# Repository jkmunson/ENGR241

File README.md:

# ENGR241
This was an old repository used to collaborate on group projects in ENGR241, Circuits II

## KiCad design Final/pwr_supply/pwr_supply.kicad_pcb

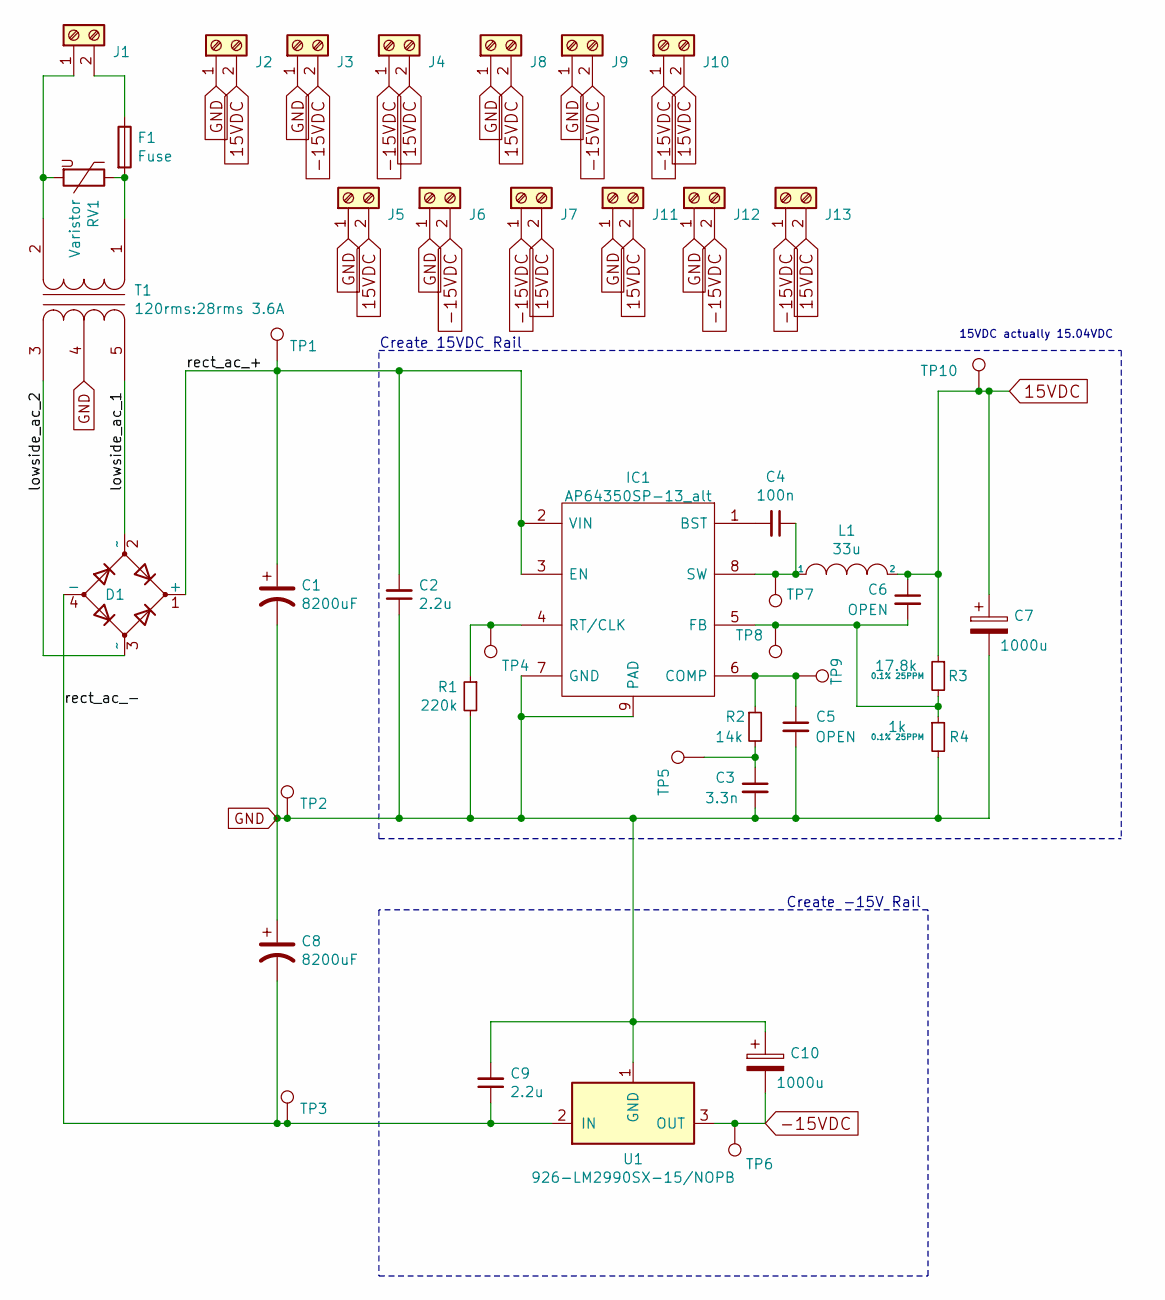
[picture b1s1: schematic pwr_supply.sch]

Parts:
C1, C8: 8200uF; CP_Radial_D30.0mm_P10.00mm_SnapIn
C2, C9: 2.2u; C_1210_3225Metric_Pad1.42x2.65mm_HandSolder
C3: 3.3n; C_1210_3225Metric_Pad1.42x2.65mm_HandSolder
C4: 100n; C_1210_3225Metric_Pad1.42x2.65mm_HandSolder
C5, C6: OPEN; C_1210_3225Metric_Pad1.42x2.65mm_HandSolder
C7, C10: 1000u; CP_Radial_D16.0mm_P7.50mm
D1: D_Bridge_+AA-; Diode_Bridge_19.0x3.5x10.0mm_P5.0mm
F1: Fuse; 00318370
IC1: AP64350SP-13_alt; SOIC127P600X163-9N; Mouser Part Number 621-AP64350SP-13
J1, J2, J3, J4, J5, J6, J7, J8, J9, J10, J11, J12, J13: Screw_Terminal_01x02; TerminalBlock_bornier-2_P5.08mm
L1: 33u; 12RS333C
R1: 220k; C_1210_3225Metric_Pad1.42x2.65mm_HandSolder
R2: 14k; C_1210_3225Metric_Pad1.42x2.65mm_HandSolder
R3: 17.8k; C_1210_3225Metric_Pad1.42x2.65mm_HandSolder; Tolerance 0.1% 25PPM
R4: 1k; C_1210_3225Metric_Pad1.42x2.65mm_HandSolder; Tolerance 0.1% 25PPM
RV1: Varistor; RV_Disc_D16.5mm_W6.7mm_P7.5mm
T1: 120rms:28rms 3.6A; Transformer_Entry
TP1, TP2, TP3, TP4, TP5, TP6, TP7, TP8, TP9, TP10: TestPoint; PinHeader_1x01_P2.54mm_Vertical
U1: 926-LM2990SX-15/NOPB; TO-263-3_TabPin2

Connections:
15VDC: C6.1, C7.1, J2.2, J4.2, J5.2, J7.2, J8.2, J10.2, J11.2, J13.2, L1.2, L1.4, R3.1, TP10.1
-15VDC: C10.2, J3.2, J4.1, J6.2, J7.1, J9.2, J10.1, J12.2, J13.1, TP6.1, U1.3 (OUT)
/lowside_ac_1: D1.2 (~~), T1.5 (SB)
/lowside_ac_2: D1.3 (~~), T1.3 (SA)
/rect_ac_+: C1.1, C2.2, D1.1 (+), IC1.2 (VIN), IC1.3 (EN), TP1.1
/rect_ac_-: C8.2, C9.1, D1.4 (-), TP3.1, U1.2 (IN)
GND: C1.2, C2.1, C3.2, C5.2, C7.2, C8.1, C9.2, C10.1, IC1.7 (GND), IC1.9 (PAD), J2.1, J3.1, J5.1, J6.1, J8.1, J9.1, J11.1, J12.1, R1.2, R4.2, T1.4 (SC), TP2.1, U1.1 (GND)
unnamed: C3.1, R2.2, TP5.1
unnamed: C4.1, IC1.8 (SW), L1.1, L1.3, TP7.1
unnamed: C4.2, IC1.1 (BST)
unnamed: C5.1, IC1.6 (COMP), R2.1, TP9.1
unnamed: C6.2, IC1.5 (FB), R3.2, R4.1, TP8.1
unnamed: F1.1, J1.2
unnamed: F1.2, RV1.1, T1.1 (AA)
unnamed: IC1.4 (RT/CLK), R1.1, TP4.1
unnamed: J1.1, RV1.2, T1.2 (AB)

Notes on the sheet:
Create 15VDC Rail
15VDC actually 15.04VDC
Create -15V Rail

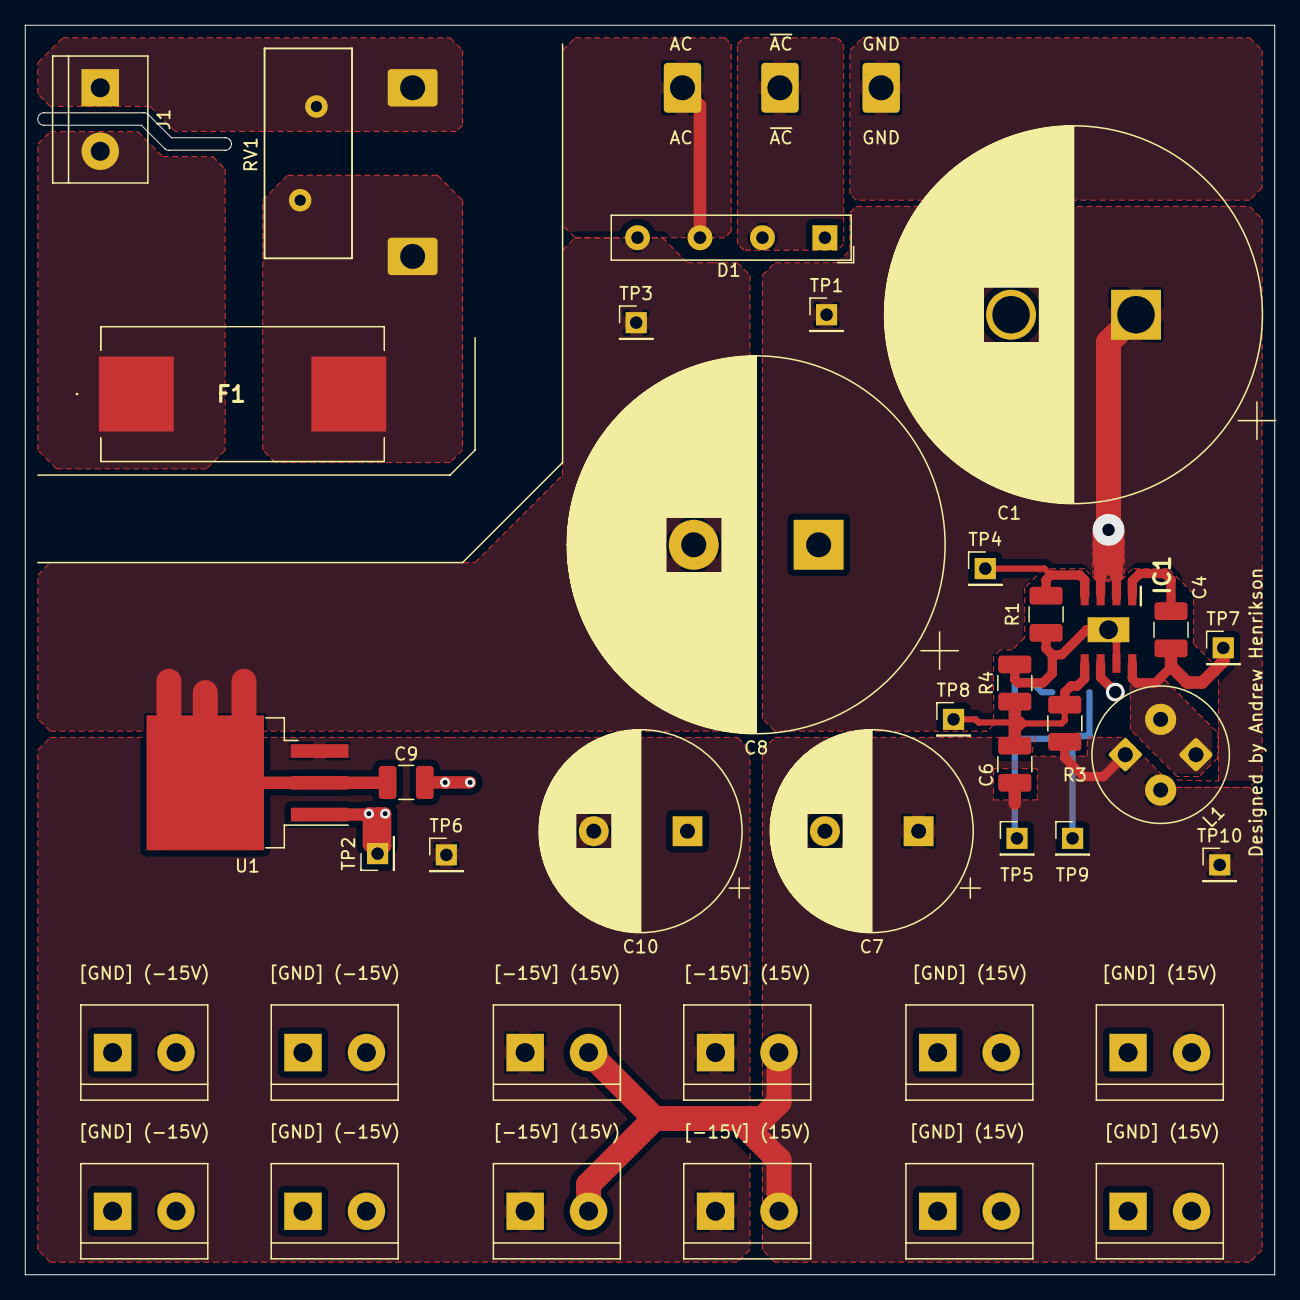
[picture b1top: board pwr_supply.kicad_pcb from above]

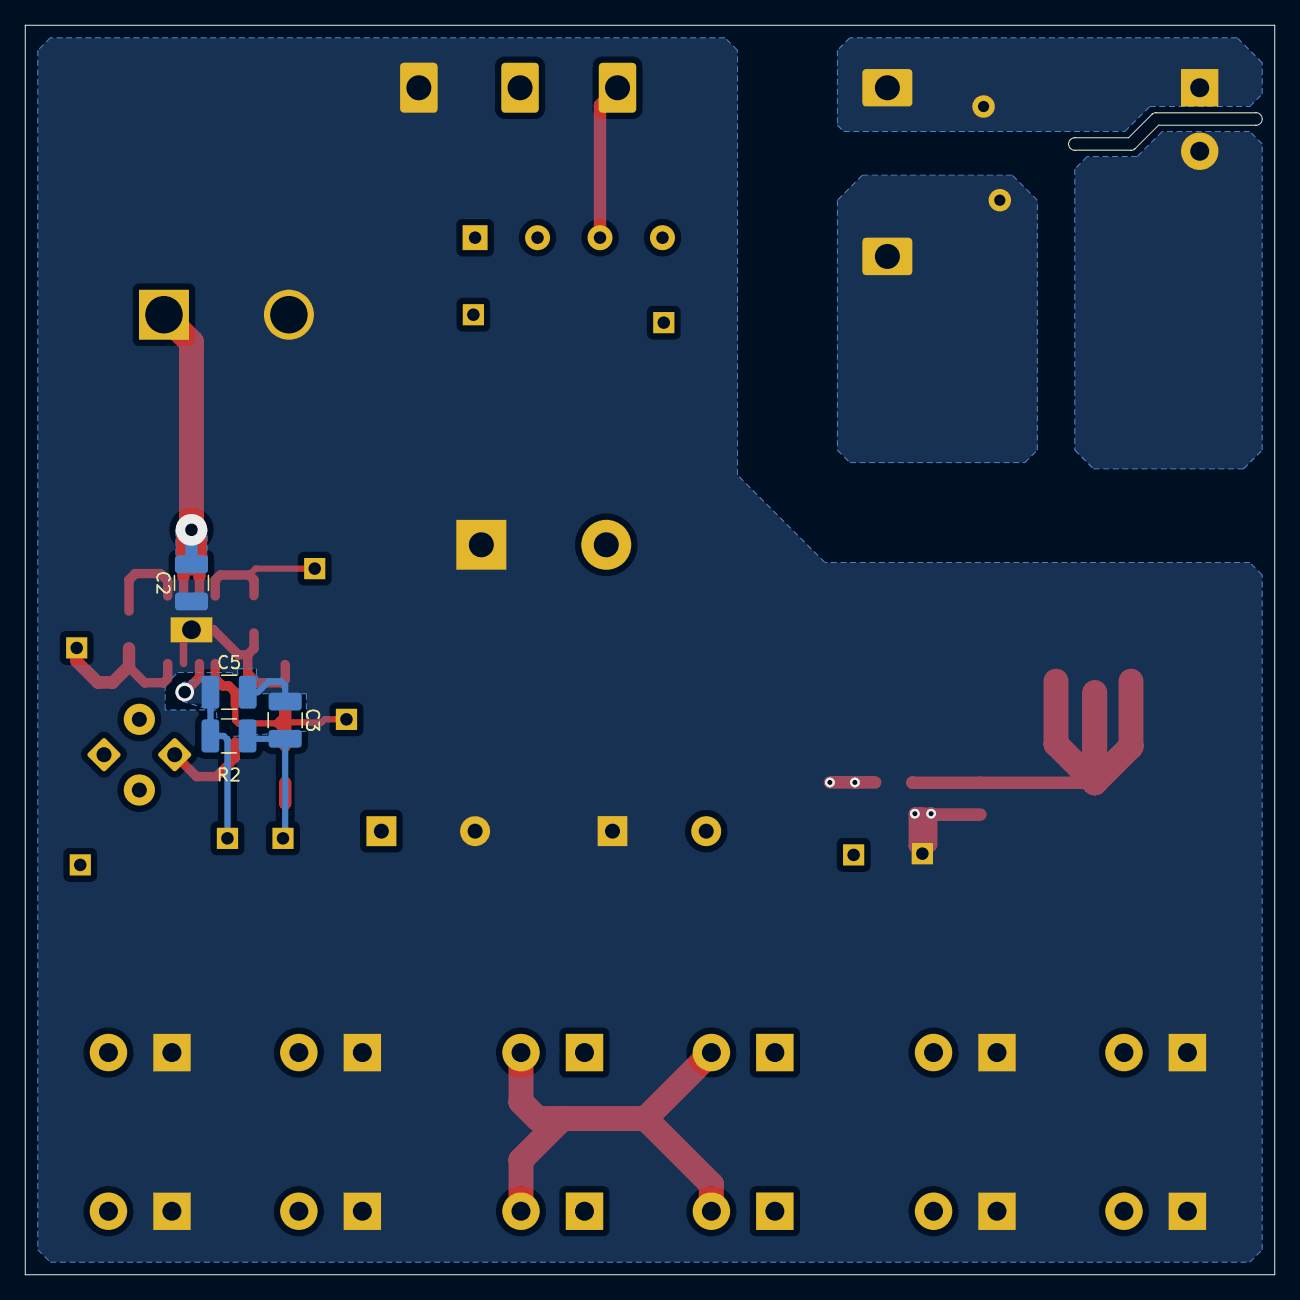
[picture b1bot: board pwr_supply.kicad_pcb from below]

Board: 2 copper layers, 100.0 x 100.0 mm, 44 parts (4 on the bottom side), 16 nets.

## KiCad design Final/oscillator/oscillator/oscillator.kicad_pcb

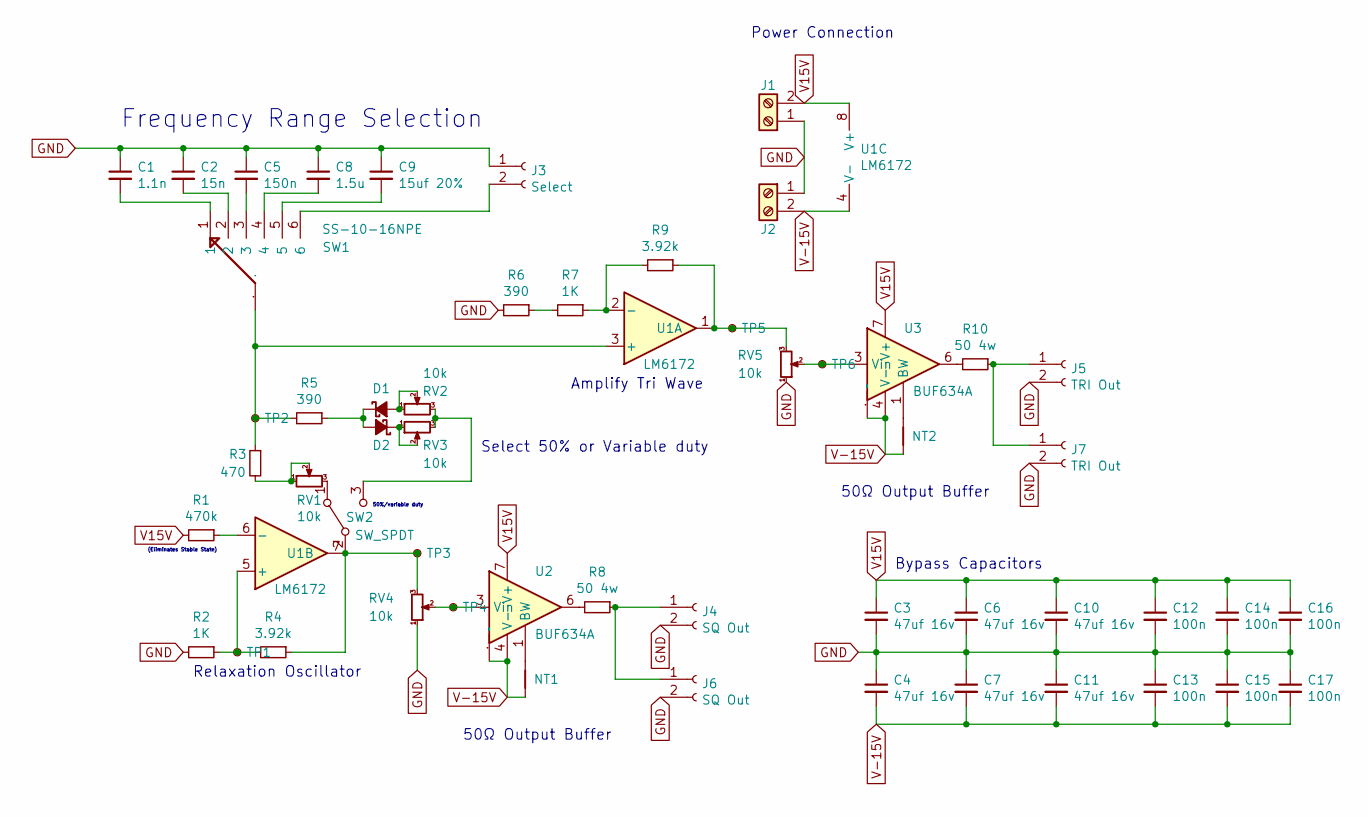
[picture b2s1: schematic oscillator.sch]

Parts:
C1: 1.1n; C_1210_3225Metric_Pad1.42x2.65mm_HandSolder
C2: 15n; C_1210_3225Metric_Pad1.42x2.65mm_HandSolder
C3, C4, C6, C7, C10, C11: 47uf 16v; C_1210_3225Metric_Pad1.42x2.65mm_HandSolder
C5: 150n; C_1210_3225Metric_Pad1.42x2.65mm_HandSolder
C8: 1.5u; C_1210_3225Metric_Pad1.42x2.65mm_HandSolder
C9: 15uf 20%; C_1210_3225Metric_Pad1.42x2.65mm_HandSolder
C12, C13, C14, C15, C16, C17: 100n; C_1210_3225Metric_Pad1.42x2.65mm_HandSolder
D1, D2: sch; D_SOD-123F
J1, J2: V15V_IN; TerminalBlock_bornier-2_P5.08mm
J3: Select; PinHeader_1x02_P2.54mm_Vertical
J4, J6: SQ Out; PinHeader_1x02_P2.54mm_Vertical
J5, J7: TRI Out; PinHeader_1x02_P2.54mm_Vertical
NT1, NT2: Net-Tie_2; SolderJumper-2_P1.3mm_Open_TrianglePad1.0x1.5mm
R1: 470k; C_1210_3225Metric_Pad1.42x2.65mm_HandSolder
R2, R7: 1K; R_1210_3225Metric_Pad1.42x2.65mm_HandSolder
R3: 470; R_1210_3225Metric_Pad1.42x2.65mm_HandSolder
R4, R9: 3.92k; R_1210_3225Metric_Pad1.42x2.65mm_HandSolder
R5, R6: 390; R_1210_3225Metric_Pad1.42x2.65mm_HandSolder
R8, R10: 50 4w; R_2816_7142Metric_Pad3.20x4.45mm_HandSolder
RV1, RV2, RV3, RV4, RV5: 10k; RK09K1130A5R
SW1: SS-10-16NPE; SS-10-16NP-E
SW2: SW_SPDT; 100SP1T1B4M2QE
TP1, TP2, TP3, TP4, TP5, TP6: TestPoint_Small; PinHeader_1x01_P1.00mm_Vertical
U1: LM6172; SOIC-8_3.9x4.9mm_P1.27mm
U2, U3: BUF634A; SOIC-8-1EP_3.9x4.9mm_P1.27mm_EP2.514x3.2mm_ThermalVias; Mouser# BUF634AIDR

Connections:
GND: C1.1, C2.1, C3.2, C4.1, C5.1, C6.2, C7.1, C8.1, C9.1, C10.2, C11.1, C12.2, C13.1, C14.2, C15.1, C16.2, C17.1, J1.1, J2.1, J3.1, J4.2, J5.2, J6.2, J7.2, R2.2, R6.2, RV4.1, RV5.1
unnamed: C1.2, SW1.1
unnamed: C2.2, SW1.2
unnamed: C5.2, SW1.3
unnamed: C8.2, SW1.4
unnamed: C9.2, SW1.5
unnamed: D1.1 (K), D2.2 (A), R5.1
unnamed: D1.2 (A), RV2.1, RV2.2
unnamed: D2.1 (K), RV3.1, RV3.2
unnamed: J3.2, SW1.6
unnamed: J4.1, J6.1, R8.1
unnamed: J5.1, J7.1, R10.1
unnamed: NT1.1, U2.1 (BW)
unnamed: NT2.1, U3.1 (BW)
unnamed: R1.1, U1.6 (-)
unnamed: R2.1, R4.2, TP1.1, U1.5 (+)
unnamed: R3.1, R5.2, SW1.C, TP2.1, U1.3 (+)
unnamed: R3.2, RV1.1, RV1.2
unnamed: R4.1, RV4.3, SW2.2 (B), TP3.1, U1.7
unnamed: R6.1, R7.2
unnamed: R7.1, R9.2, U1.2 (-)
unnamed: R8.2, U2.6
unnamed: R9.1, RV5.3, TP5.1, U1.1
unnamed: R10.2, U3.6
unnamed: RV1.3, SW2.1 (A)
unnamed: RV2.3, RV3.3, SW2.3 (C)
unnamed: RV4.2, TP4.1, U2.3 (Vin)
unnamed: RV5.2, TP6.1, U3.3 (Vin)
V15V: C3.1, C6.1, C10.1, C12.1, C14.1, C16.1, J1.2, R1.2, U1.8 (V+), U2.7 (V+), U3.7 (V+)
V-15V: C4.2, C7.2, C11.2, C13.2, C15.2, C17.2, J2.2, NT1.2, NT2.2, U1.4 (V-), U2.4 (V-), U2.9 (PPAD), U3.4 (V-), U3.9 (PPAD)

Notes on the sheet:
(Eliminates Stable State)
50%/variable duty
Frequency Range Selection
Amplify Tri Wave
50Ω Output Buffer
Relaxation Oscillator
Select 50% or Variable duty
Bypass Capacitors
Power Connection

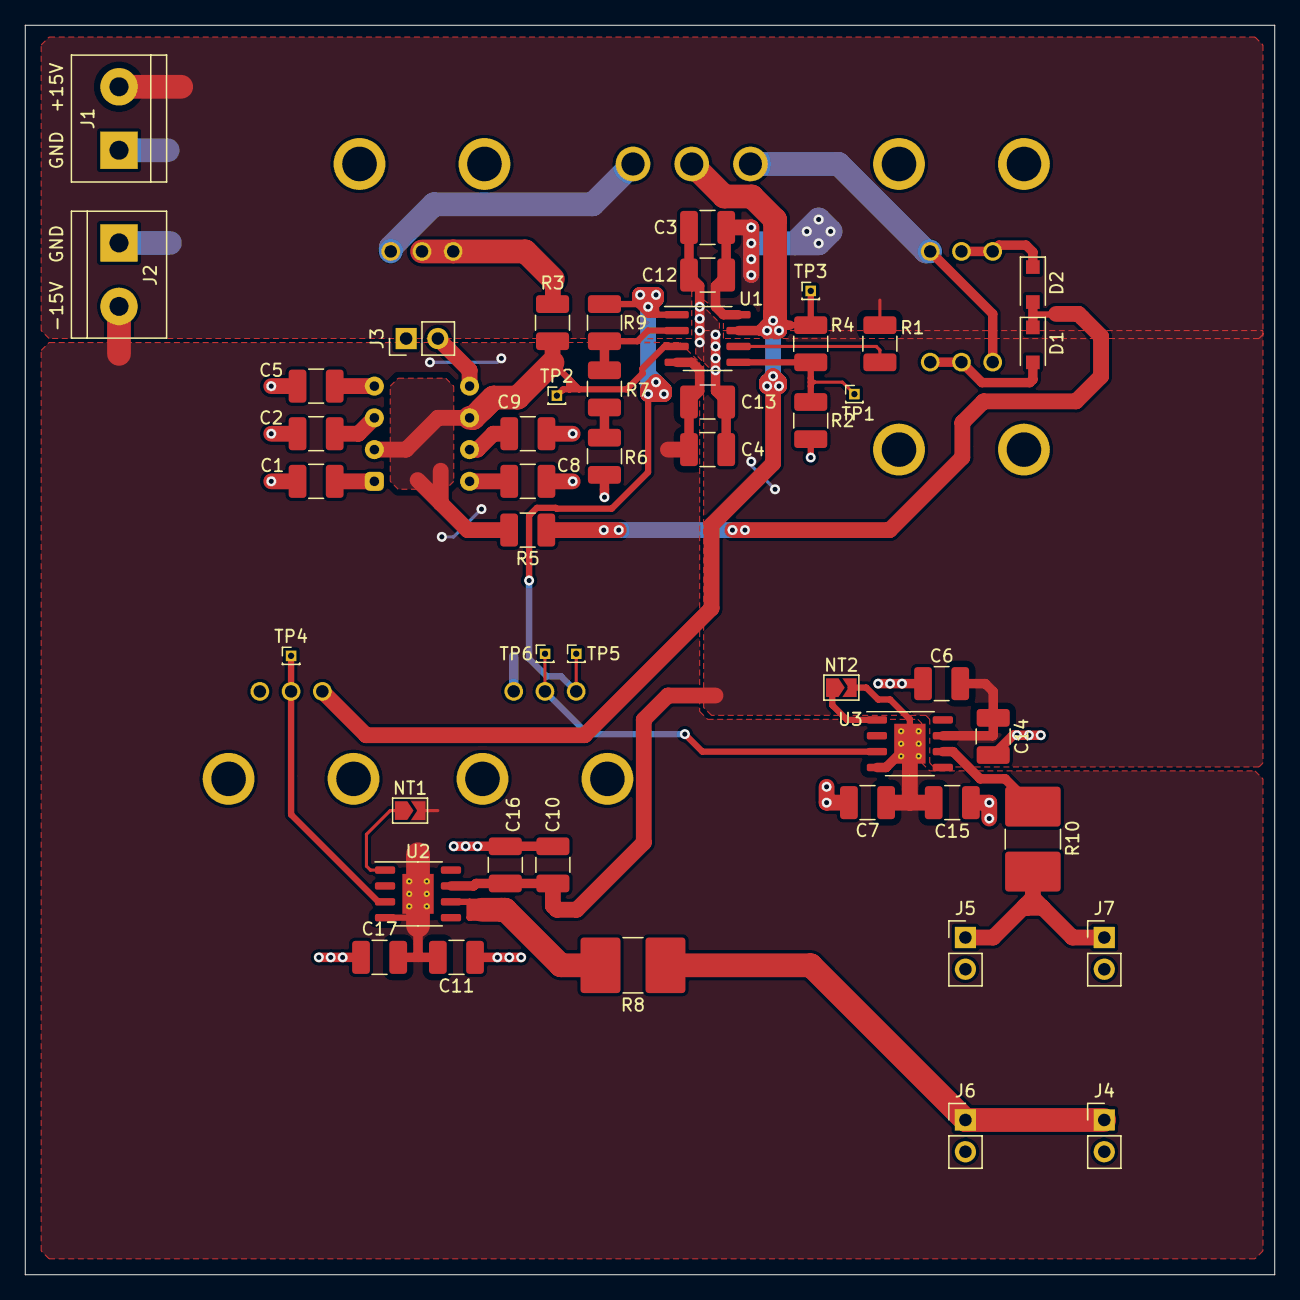
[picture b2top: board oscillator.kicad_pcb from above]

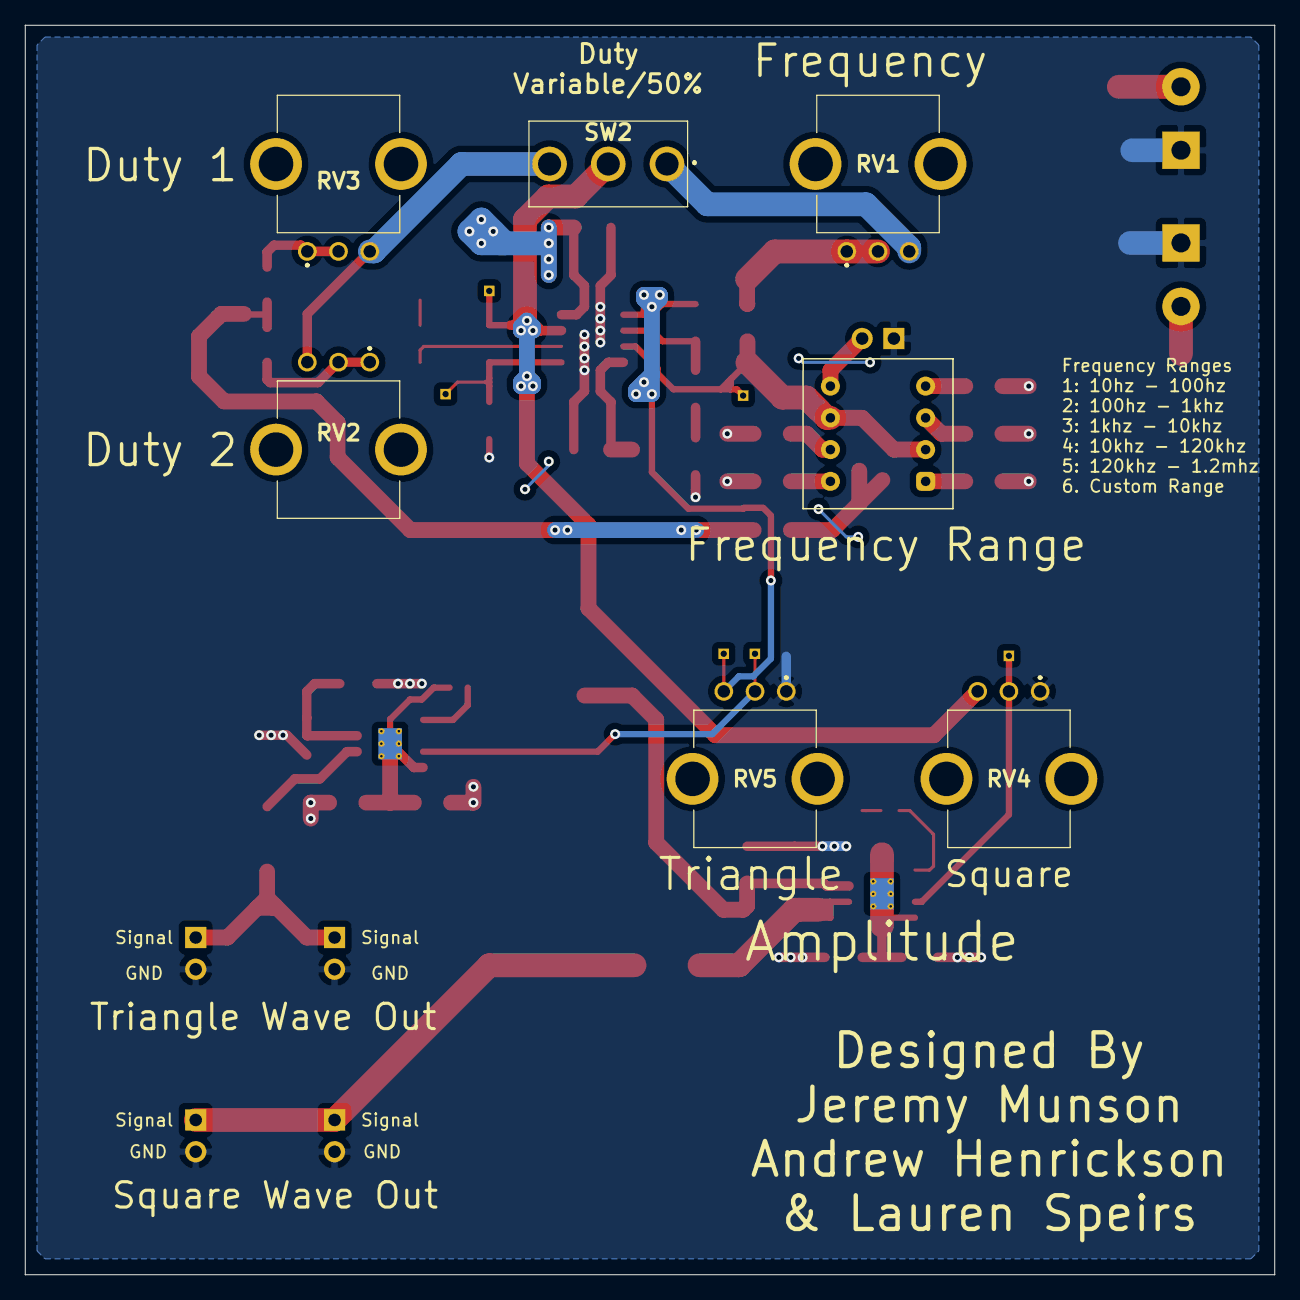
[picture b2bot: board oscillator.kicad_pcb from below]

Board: 2 copper layers, 100.0 x 100.0 mm, 54 parts (7 on the bottom side), 30 nets.

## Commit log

2021-03-05 Added Example File.txt
2021-03-05 Modified Example File.txt
2021-03-05 Added schematic, Report stuff.
2021-03-05 Changed some bits in the report. Restructured. Added in my parts.
2021-03-08 Added images related to the laplace lab.
2021-03-12 Updated circuit diagram
2021-03-12 Finalizing the report for Laplace.
2021-03-12 Added 5vpp to circuit diagram. Darkened it for better contrast.
2021-03-12 Add files via upload
    laplace part in orcad simulation
2021-03-18 Update Transfer Function.tex
    Added a table showing the measured component values
2021-03-19 Create RC Low Pass Filter Lab
2021-03-20 Finished transfer function lab report calculations
2021-03-21 Create images
2021-03-26 Update Passive Filters.tex
    added to conclusion and a few more photos in appendix.
2021-03-26 Finalizing report
2021-05-01 Add files via upload
    Images of the test board
